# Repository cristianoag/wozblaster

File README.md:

# The Wozblaster (Reloaded)

## Introduction 
The WozBlaster OPL4 cartridge is a sound expansion device designed for the MSX platform. This cartridge enables a range of additional audio capabilities for the MSX, including support for both FM synthesis and wavetable synthesis. 

At its core is the OPL4 (FM Operator Type-L4) sound chip, which was developed by Yamaha and used in a variety of electronic musical instruments and computer sound cards. 

With the WozBlaster OPL4 cartridge, MSX computer users can enjoy high-quality sound and create complex musical arrangements with ease.

.jpg)

The WozBlaster cartridge is an external sound device designed for the MSX platform. It is a clone of the Moonsound and allows access to the advanced capabilities of the OPL4 sound chip for MSX games and other OPL4-compatible music software. The cartridge was originally designed by Gustavo Iriarte.

The OPL4 sound chip from Yamaha is typically paired with a YAC513 floating-point DAC chip, or an alternative compatible DAC chip. The YMF278 is an enhanced version of the OPL3 and, although not officially part of the standard, has been widely adopted by the MSX community, particularly in Europe.

Moonsound clones generally come equipped with 1 MB of sample-RAM and a 2 MB Yamaha YRW801-M General MIDI ROM. Although the board has the capacity to address more than 1 MB of memory, the original version of the Wozblaster only had two 512K memory chips.

It's worth noting that the original Wozblaster PCB cannot be fitted into a traditional MSX cartridge case. Additionally, as detailed in the building instructions, the audio jack holes on the original board are quite small, which made it difficult to find a connector that would fit.

## Original Wozblaster

Image below shows the original Wozblaster cartridge PCB:

|PCB Side 1|PCB Side 2|
|---|---|
|.jpg)|.jpg)|

A few reloaded versions of the WozBlaster cartridge have been created with appropriately-sized holes to fit both Konami and Patola cartridge cases. Additionally, the audio jack holes have been enlarged to accommodate most common audio jack connectors. Some versions of the cartridge are still a work in progress.

## Reloaded Versions

Currently, the following versions of the WozBlaster cartridge are available (please note that this list is subject to change as new versions become available):

* [Wozblaster Reloaded v1.1](/hardware/reloaded_v1.1) - Based on the original circuit, this version features a combination of through-hole and surface-mount components. The board is smaller and can fit in both Konami and Patola cases. (tested and working)

|PCB Side 1|PCB Side 2|
|---|---|
|.jpg)|.jpg)|

* [Wozblaster Reloaded v1.3](/hardware/reloaded_v1.3) - This version replaces the old 27C160 EPROM with an AM29F016B flash memory, and all passive components are 0603 SMD. The sound is injected back to SOUNDIN in mono. The board is smaller and can fit in both Konami and Patola cases. (abandoned)
  
* [Wozblaster Reloaded v3.3](/hardware/reloaded_v3.3/) - Version based on the UDA1334 DAC, and using the [Adafruit A1334 DAC Module](https://github.com/adafruit/Adafruit-UDA1334A-I2S-Stereo-DAC-PCB) to perform the digital to analog conversion. It is injecting audio back into the SOUNDIN MSX pin. It features 1MB of RAM and 2MB of ROM with MIDI compatible samples. (tested and working)

|PCB Side 1|PCB Side 2|
|---|---|
|||

* [Wozblaster Reloaded v4.0](/hardware/reloaded_v4.0/) - Evolution of v3.3 featuring a 2MB CY62167ELL RAM integrated. It also mixes the computer SOUNDIN. (tested and working)

|PCB Side 1|PCB Side 2|
|---|---|
|.jpg)|.jpg)|

* [Wozblaster Reloaded v4.5](/hardware/reloaded_v4.5/) - This version is now using the EPM7064STC44 (or EPM7032STC400) CPLD to replace the GAL16V8D it also better isolates the audio channels  before injecting them as mono back to the MSX SOUNDIN. (tested and working)

|PCB Side 1|PCB Side 2|
|---|---|
|.jpg)|.jpg)|

## Bill of Materials

The Bill of Materials (BOM) for each version of the WozBlaster cartridge is available in the respective page. The BOM includes a list of all the components needed to build the cartridge, as well as links to purchase the components online.

## Box and Inlay Trays

The Wozblaster Reloaded has a box designed by Adriano Souza to fit the cartridge. The box is available in the [box](/box) folder.

Although a paper inlay is provided to secure the cartridge inside the box, it is  recommended to use a plastic insert inner tray (bed) for additional protection, especially during transportation. These trays can be purchased from AliExpress at the following link: [AliExpress Tray](https://s.click.aliexpress.com/e/_DDVBv2D).

## Resources

This GitHub repository contains all of the resources needed to build both the original WozBlaster cartridge and the reloaded versions. For detailed instructions, you can refer to the article I wrote, which includes an updated bill of materials (BOM) with links to purchase the required components. You can find the article at https://theretrohacker.com/2022/12/31/blasting-sound-for-your-msx-the-wozblaster-reloaded/.

The update on the v3.1 development has been posted on a short YouTube video in english [here](https://youtu.be/J95RrFSF2NM). 

The update on v3.2 is available on a quick video [here](https://www.youtube.com/shorts/V5VmL33uvzE). 

Each folder contains detailed Bill of Materials for each version of the board, as well as the Gerber files needed to manufacture the PCBs. 

## License 

This work is licensed under a [Creative Commons Attribution-NonCommercial-ShareAlike 4.0 International License](http://creativecommons.org/licenses/by-nc-sa/4.0/).

* If you remix, transform, or build upon the material, you must distribute your contributions under the same license as the original.
* You may not use the material for commercial purposes.
* You must give appropriate credit, provide a link to the license, and indicate if changes were made. You may do so in any reasonable manner, but not in any way that suggests the licensor endorses you or your use.

**ATTENTION**

This project was made for the retro community and not for commercial purposes. So only retro hardware forums and individual people can build this project.

THE SALE OF ANY PART OF THIS PROJECT WITHOUT EXPRESS AUTHORIZATION IS PROHIBITED!

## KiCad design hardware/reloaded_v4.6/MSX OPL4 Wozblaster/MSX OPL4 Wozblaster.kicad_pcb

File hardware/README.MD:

# The Wozblaster (Reloaded)

## Content of this folder:

* [27C160 Adapter](/hardware/27c160-tl866-adapter) - This folder contains the files necessary to build an adapter that allows you to program the 27C160 EPROM on inexpensive TL866 programmers.
* [GAL16V8 JEDEC](/hardware/gal16v8d) - This folder contains the fuse file required to program the GAL16V8 SPLD with the selection circuit needed for the Wozblasters.
* [YRW801-M ROM] - This folder contains the binary content needed to program flash or EPROMs with the contents of the YRW801-M (MIDI Samples).
* [Wozblaster v1](hardware/v1) - This folder contains the original Wozblaster board created by Gustavo Iriarte. (Released)
* [Wozblaster Reloaded v1.1](/hardware/reloaded_v1.1) - Based on the original circuit, this version features a combination of through-hole and surface-mount components. The board is smaller and can fit in both Konami and Patola cases. (Released)
* [Wozblaster Reloaded v1.2](/hardware/reloaded_v1.2) - This version replaces the old 27C160 EPROM with an AM29F016B flash, and all passive components are 0603 SMD. The sound is injected back to SOUNDIN in mono. The board is smaller and can fit in both Konami and Patola cases. (In development)
* [Wozblaster Reloaded v2.0](/hardware/reloaded_v2) - This version features an AM29F016B flash in place of the 27C160 EPROM, all passive components are 0603 SMD, and the YAC513 DAC is replaced by a NEC UPD6376. The sound is injected back to SOUNDIN in mono, and the LF347 OP Amps are replaced with 4558s. The audio circuit has been improved, and the board is smaller and can fit in both Konami and Patola cases. (In development)

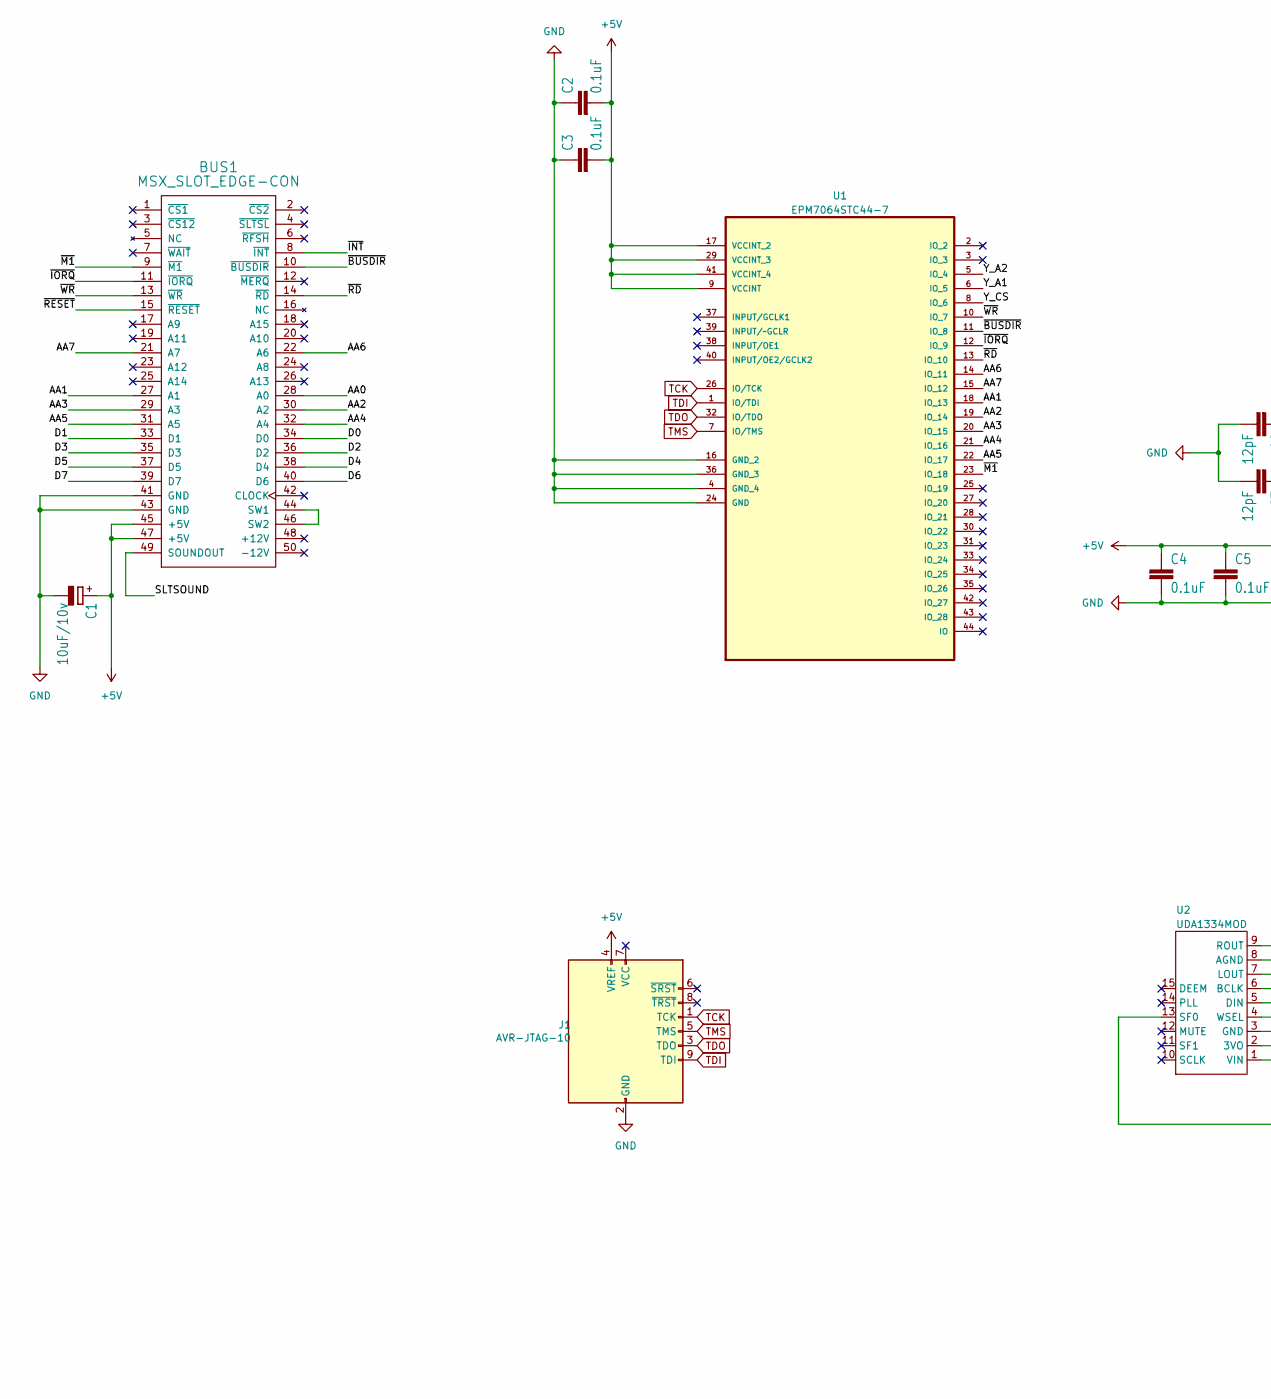
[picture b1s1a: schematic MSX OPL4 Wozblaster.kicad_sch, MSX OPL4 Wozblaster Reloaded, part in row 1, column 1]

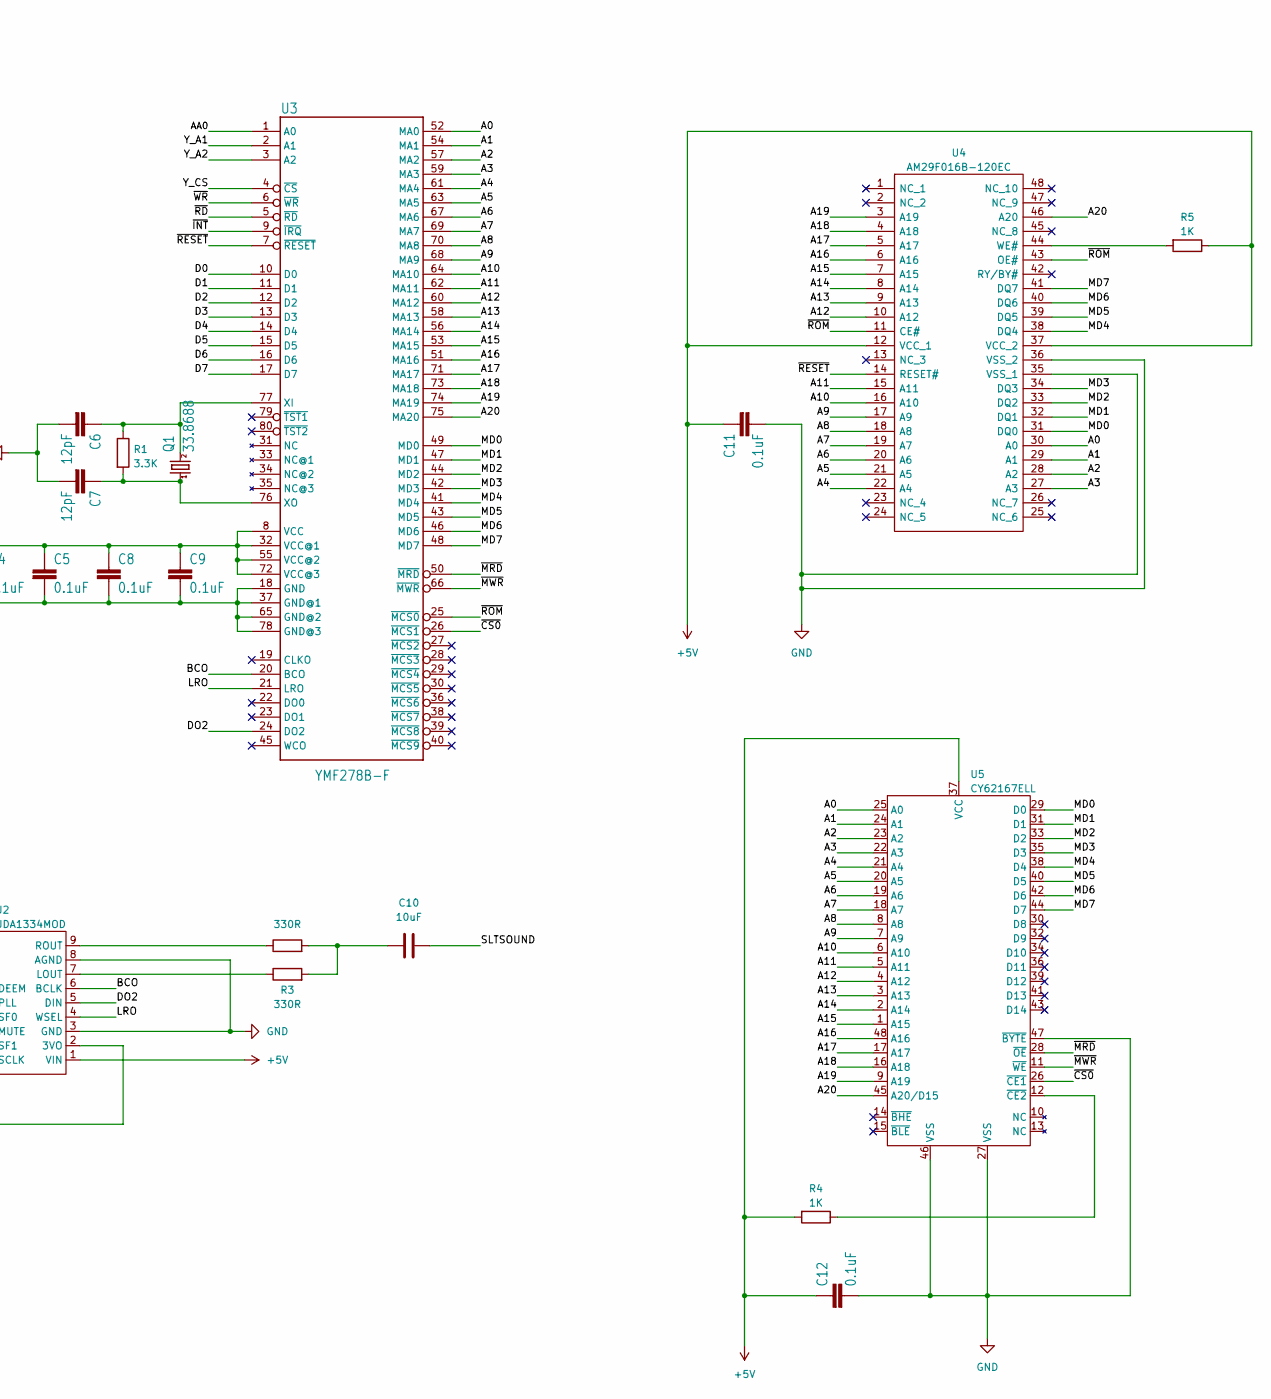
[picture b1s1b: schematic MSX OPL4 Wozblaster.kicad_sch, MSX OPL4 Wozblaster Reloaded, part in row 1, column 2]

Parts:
BUS1: MSX_SLOT_EDGE-CON; msx_cartridge; MPN n/a
C1: 10uF/10v; CP_EIA-3216-18_Kemet-A
C2, C3, C4, C5, C8, C9, C11, C12: 0.1uF; C_0603_1608Metric
C6, C7: 12pF; C_0603_1608Metric
C10: 10uF; C_0603_1608Metric
J1: AVR-JTAG-10; PinHeader_2x05_P2.54mm_Vertical
Q1: 33.8688; Crystal_HC49-U_Vertical
R1: 3.3K; R_0603_1608Metric
R2, R3: 330R; R_0603_1608Metric
R4, R5: 1K; R_0603_1608Metric
U1: EPM7064STC44-7; QFP80P1200X1200X120-44N; MPN EPM7064STC44-7
U2: UDA1334MOD
U3: YMF278B-F; 80-QFP
U4: AM29F016B-120EC; SOP50P2000X120-48N; Manufacturer_Part_Number AM29F016B-120EC
U5: CY62167ELL; SOP50P2000X120-48N

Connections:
+5V: BUS1.45 (+5V), BUS1.47 (+5V), C1.1 (+), C2.2, C3.2, C4.1, C5.1, C8.1, C9.1, C11.1, C12.1, J1.4 (VREF), R4.2, R5.1, U1.9 (VCCINT), U1.17 (VCCINT_2), U1.29 (VCCINT_3), U1.41 (VCCINT_4), U2.1 (VIN), U3.8 (VCC), U3.32 (VCC@1), U3.55 (VCC@2), U3.72 (VCC@3), U4.12 (VCC_1), U4.37 (VCC_2), U5.37 (VCC)
/A0: U3.52 (MA0), U4.30 (A0), U5.25 (A0)
/A1: U3.54 (MA1), U4.29 (A1), U5.24 (A1)
/A2: U3.57 (MA2), U4.28 (A2), U5.23 (A2)
/A3: U3.59 (MA3), U4.27 (A3), U5.22 (A3)
/A4: U3.61 (MA4), U4.22 (A4), U5.21 (A4)
/A5: U3.63 (MA5), U4.21 (A5), U5.20 (A5)
/A6: U3.67 (MA6), U4.20 (A6), U5.19 (A6)
/A7: U3.69 (MA7), U4.19 (A7), U5.18 (A7)
/A8: U3.70 (MA8), U4.18 (A8), U5.8 (A8)
/A9: U3.68 (MA9), U4.17 (A9), U5.7 (A9)
/A10: U3.64 (MA10), U4.16 (A10), U5.6 (A10)
/A11: U3.62 (MA11), U4.15 (A11), U5.5 (A11)
/A12: U3.60 (MA12), U4.10 (A12), U5.4 (A12)
/A13: U3.58 (MA13), U4.9 (A13), U5.3 (A13)
/A14: U3.56 (MA14), U4.8 (A14), U5.2 (A14)
/A15: U3.53 (MA15), U4.7 (A15), U5.1 (A15)
/A16: U3.51 (MA16), U4.6 (A16), U5.48 (A16)
/A17: U3.71 (MA17), U4.5 (A17), U5.17 (A17)
/A18: U3.73 (MA18), U4.4 (A18), U5.16 (A18)
/A19: U3.74 (MA19), U4.3 (A19), U5.9 (A19)
/A20: U3.75 (MA20), U4.46 (A20), U5.45 (A20/D15)
/AA0: BUS1.28 (A0), U3.1 (A0)
/AA1: BUS1.27 (A1), U1.18 (IO_13)
/AA2: BUS1.30 (A2), U1.19 (IO_14)
/AA3: BUS1.29 (A3), U1.20 (IO_15)
/AA4: BUS1.32 (A4), U1.21 (IO_16)
/AA5: BUS1.31 (A5), U1.22 (IO_17)
/AA6: BUS1.22 (A6), U1.14 (IO_11)
/AA7: BUS1.21 (A7), U1.15 (IO_12)
/BCO: U2.6 (BCLK), U3.20 (BCO)
/D0: BUS1.34 (D0), U3.10 (D0)
/D1: BUS1.33 (D1), U3.11 (D1)
/D2: BUS1.36 (D2~), U3.12 (D2)
/D3: BUS1.35 (D3), U3.13 (D3)
/D4: BUS1.38 (D4), U3.14 (D4)
/D5: BUS1.37 (D5), U3.15 (D5)
/D6: BUS1.40 (D6), U3.16 (D6)
/D7: BUS1.39 (D7), U3.17 (D7)
/DO2: U2.5 (DIN), U3.24 (DO2)
/LRO: U2.4 (WSEL), U3.21 (LRO)
/MD0: U3.49 (MD0), U4.31 (DQ0), U5.29 (D0)
/MD1: U3.47 (MD1), U4.32 (DQ1), U5.31 (D1)
/MD2: U3.44 (MD2), U4.33 (DQ2), U5.33 (D2)
/MD3: U3.42 (MD3), U4.34 (DQ3), U5.35 (D3)
/MD4: U3.41 (MD4), U4.38 (DQ4), U5.38 (D4)
/MD5: U3.43 (MD5), U4.39 (DQ5), U5.40 (D5)
/MD6: U3.46 (MD6), U4.40 (DQ6), U5.42 (D6)
/MD7: U3.48 (MD7), U4.41 (DQ7), U5.44 (D7)
/SLTSOUND: BUS1.49 (SOUNDOUT), C10.2
/Y_A1: U1.6 (IO_5), U3.2 (A1)
/Y_A2: U1.5 (IO_4), U3.3 (A2)
/Y_CS: U1.8 (IO_6), U3.4 (~CS)
/~BUSDIR: BUS1.10 (~BUSDIR), U1.11 (IO_8)
/~CS0: U3.26 (~MCS1), U5.26 (~CE1)
/~INT: BUS1.8 (~INT), U3.9 (~IRQ)
/~IORQ: BUS1.11 (~IORQ), U1.12 (IO_9)
/~M1: BUS1.9 (~M1), U1.23 (IO_18)
/~MRD: U3.50 (~MRD), U5.28 (~OE)
/~MWR: U3.66 (~MWR), U5.11 (~WE)
/~RD: BUS1.14 (~RD), U1.13 (IO_10), U3.5 (~RD)
/~RESET: BUS1.15 (~RESET), U3.7 (~RESET), U4.14 (RESET#)
/~ROM: U3.25 (~MCS0), U4.11 (CE#), U4.43 (OE#)
/~WR: BUS1.13 (~WR), U1.10 (IO_7), U3.6 (~WR)
GND: BUS1.41 (GND), BUS1.43 (GND), C1.2 (-), C2.1, C3.1, C4.2, C5.2, C6.2, C7.2, C8.2, C9.2, C11.2, C12.2, J1.2 (GND), J1.10 (GND), U1.4 (GND_4), U1.16 (GND_2), U1.24 (GND), U1.36 (GND_3), U2.3 (GND), U2.8 (AGND), U3.18 (GND), U3.37 (GND@1), U3.65 (GND@2), U3.78 (GND@3), U4.35 (VSS_1), U4.36 (VSS_2), U5.27 (VSS), U5.46 (VSS), U5.47 (~BYTE)
unnamed: BUS1.44 (SW1), BUS1.46 (SW2)
unnamed: C10.1, R2.2, R3.2
unnamed: U2.2 (3VO), U2.13 (SF0)
unnamed: R3.1, U2.7 (LOUT)
unnamed: R2.1, U2.9 (ROUT)
unnamed: C6.1, Q1.2, R1.1, U3.77 (XI)
unnamed: C7.1, Q1.1, R1.2, U3.76 (XO)
unnamed: R5.2, U4.44 (WE#)
unnamed: R4.1, U5.12 (~CE2)
TCK: J1.1 (TCK), U1.26 (IO/TCK)
TDI: J1.9 (TDI), U1.1 (IO/TDI)
TDO: J1.3 (TDO), U1.32 (IO/TDO)
TMS: J1.5 (TMS), U1.7 (IO/TMS)

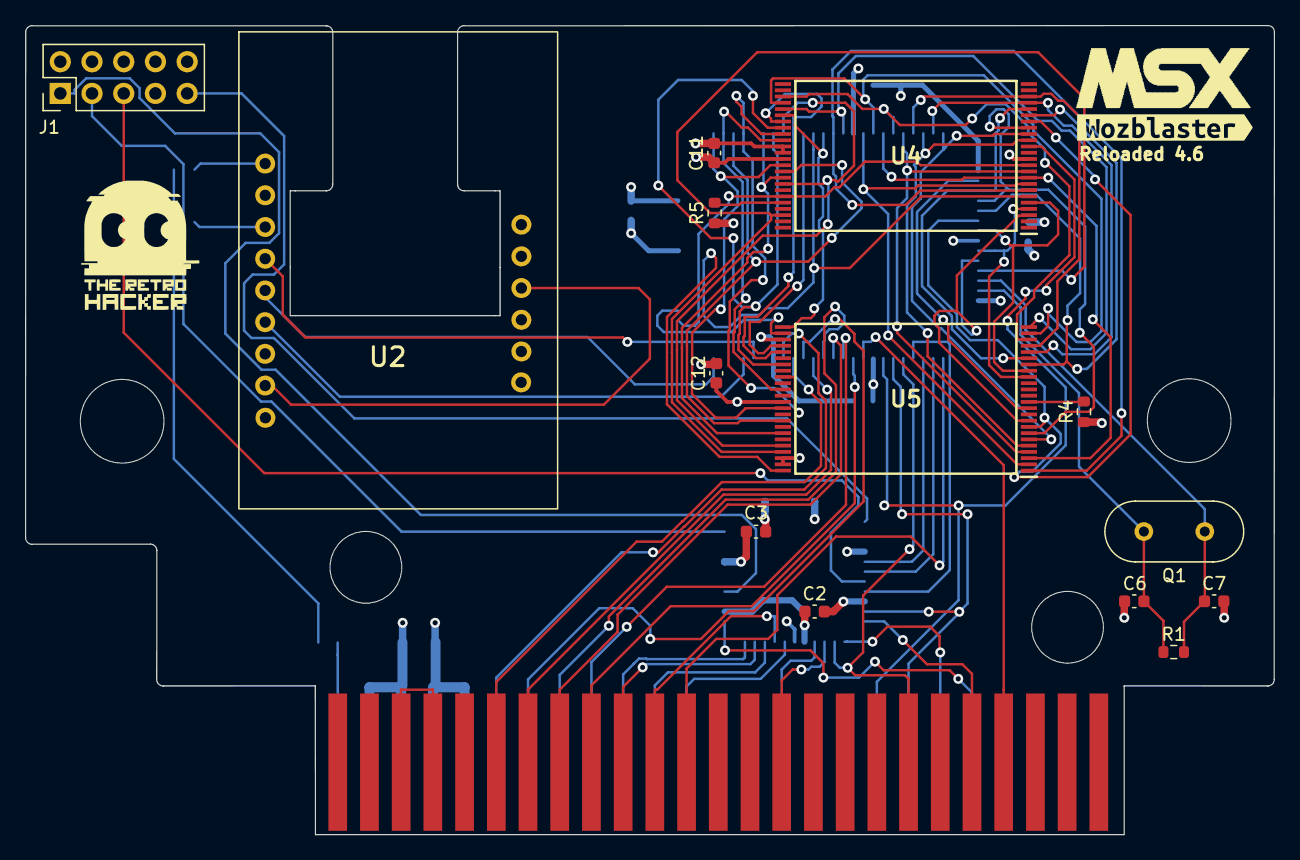
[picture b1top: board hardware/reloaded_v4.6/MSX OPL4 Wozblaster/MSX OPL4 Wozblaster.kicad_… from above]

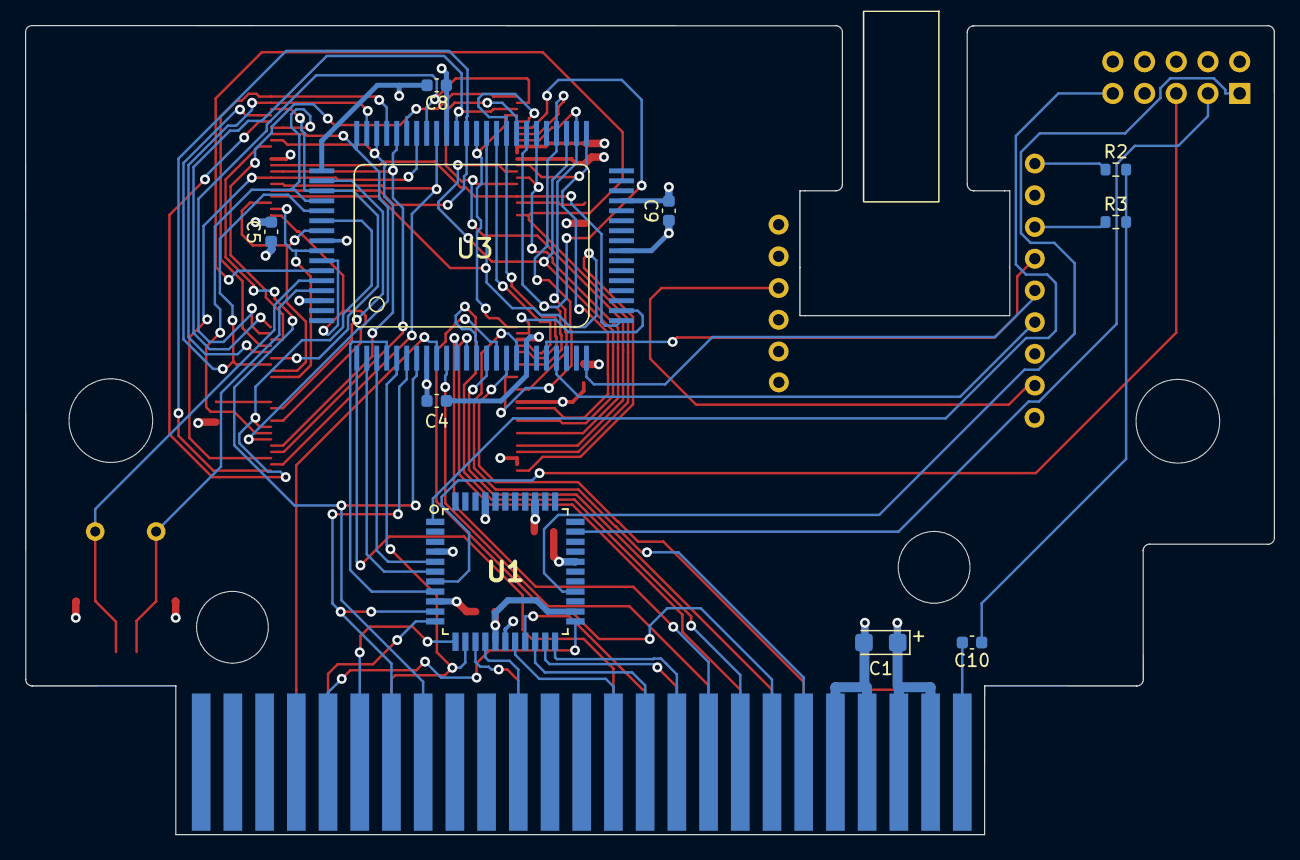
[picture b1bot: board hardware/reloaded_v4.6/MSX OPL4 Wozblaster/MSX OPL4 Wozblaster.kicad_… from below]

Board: 4 copper layers, 100.0 x 64.8 mm, 27 parts (11 on the bottom side), 78 nets.

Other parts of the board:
LOGO_MSX: LOGO_MSX
kibuzzard-670C230B: G***; kibuzzard-670C230B

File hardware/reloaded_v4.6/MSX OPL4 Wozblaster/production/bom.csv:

Designator,Footprint,Quantity,Value,LCSC Part #
C1,CP_EIA-3216-18_Kemet-A,1,10uF/10v,
C10,0603,1,10uF,
"C11, C12, C2, C3, C4, C5, C8, C9",0603,8,0.1uF,
"C6, C7",0603,2,12pF,
J1,PinHeader_2x05_P2.54mm_Vertical,1,AVR-JTAG-10,
LOGO_MSX,LOGO_MSX,1,,
Q1,Crystal_HC49-U_Vertical,1,33.8688,
R1,0603,1,3.3K,
"R2, R3",0603,2,330R,
"R4, R5",0603,2,1K,
U1,QFP80P1200X1200X120-44N,1,EPM7064STC44-7,EPM7064STC44-7
U2,UDA1334MOD,1,UDA1334MOD,
U3,80-QFP,1,YMF278B-F,
U4,SOP50P2000X120-48N,1,AM29F016B-120EC,
U5,SOP50P2000X120-48N,1,CY62167ELL,

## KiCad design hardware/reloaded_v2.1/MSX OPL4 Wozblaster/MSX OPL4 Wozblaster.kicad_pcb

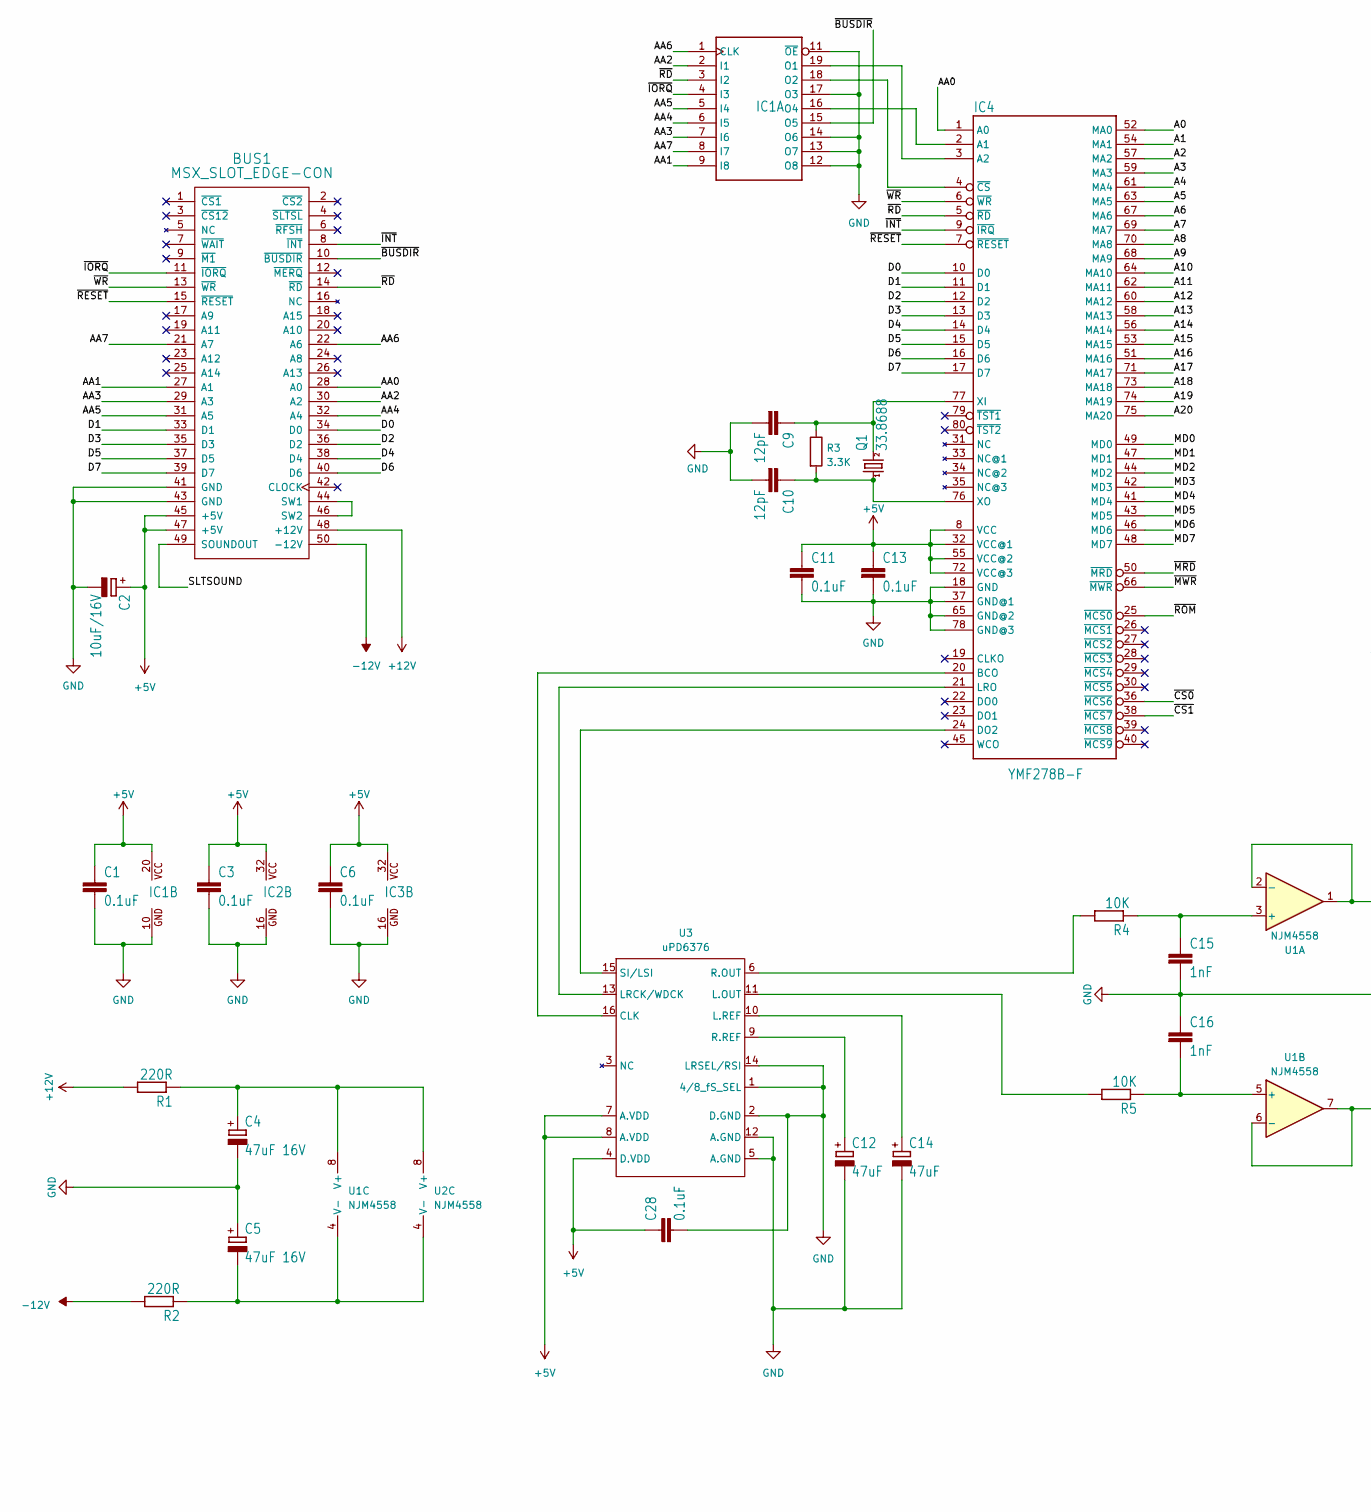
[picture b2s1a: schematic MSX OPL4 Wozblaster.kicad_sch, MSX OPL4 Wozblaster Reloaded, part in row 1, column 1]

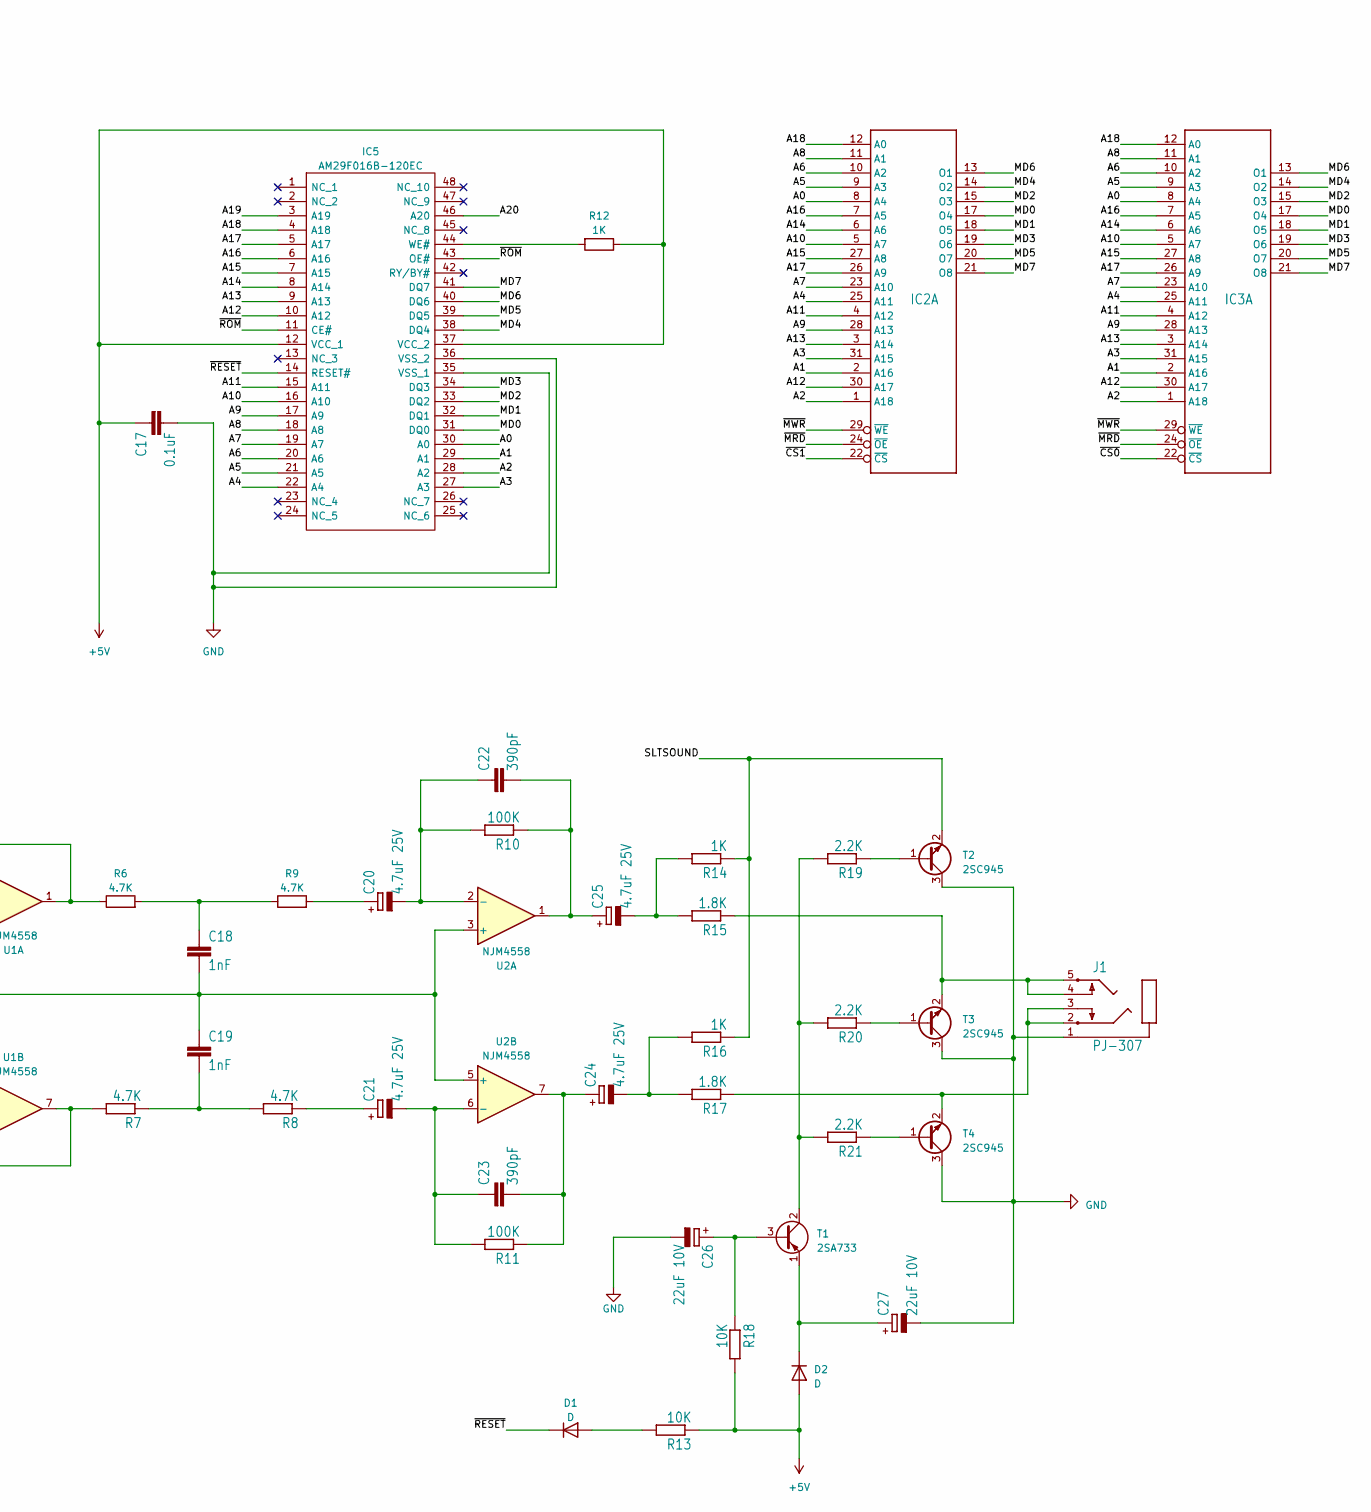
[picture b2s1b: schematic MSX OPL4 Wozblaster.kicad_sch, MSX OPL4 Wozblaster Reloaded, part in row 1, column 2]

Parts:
BUS1: MSX_SLOT_EDGE-CON; msx_cartridge; MPN n/a
C1, C3, C6, C11, C13, C17, C28: 0.1uF; C_0603_1608Metric
C2: 10uF/16V; CP_EIA-3528-21_Kemet-B
C4, C5: 47uF 16V; CP_EIA-3528-21_Kemet-B
C9, C10: 12pF; C_0603_1608Metric
C12, C14: 47uF; CP_EIA-3528-21_Kemet-B
C15, C16, C18, C19: 1nF; C_0603_1608Metric
C20, C21, C24, C25: 4.7uF 25V; CP_EIA-3216-18_Kemet-A
C22, C23: 390pF; C_0603_1608Metric
C26, C27: 22uF 10V; CP_EIA-3528-21_Kemet-B
D1, D2: D; D_A-405_P7.62mm_Horizontal
IC1: GAL16V8D; DIL20
IC2, IC3: KM684000ALG; SOP32L
IC4: YMF278B-F; 80-QFP
IC5: AM29F016B-120EC; SOP50P2000X120-48N; Manufacturer_Part_Number AM29F016B-120EC
J1: PJ-307
Q1: 33.8688; Crystal_HC49-U_Vertical
R1, R2: 220R; R_0603_1608Metric
R3: 3.3K; R_0603_1608Metric
R4, R5, R13, R18: 10K; R_0603_1608Metric
R6, R7, R8, R9: 4.7K; R_0603_1608Metric
R10, R11: 100K; R_0603_1608Metric
R12, R14, R16: 1K; R_0603_1608Metric
R15, R17: 1.8K; R_0603_1608Metric
R19, R20, R21: 2.2K; R_0603_1608Metric
T1: 2SA733; SOT-23
T2, T3, T4: 2SC945; SOT-23
U1, U2: NJM4558; SO-8_5.3x6.2mm_P1.27mm
U3: uPD6376; SO-16_5.3x10.2mm_P1.27mm

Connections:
+5V: BUS1.45 (+5V), BUS1.47 (+5V), C1.1, C2.1 (+), C3.1, C6.1, C11.1, C13.1, C17.1, C28.1, D2.2 (A), IC1.20 (VCC), IC2.32 (VCC), IC3.32 (VCC), IC4.8 (VCC), IC4.32 (VCC@1), IC4.55 (VCC@2), IC4.72 (VCC@3), IC5.12 (VCC_1), IC5.37 (VCC_2), R12.1, R13.1, R18.2, U3.4 (D.VDD), U3.7 (A.VDD), U3.8 (A.VDD)
+12V: BUS1.48 (+12V), R1.2
-12V: BUS1.50 (-12V), R2.2
/A0: IC2.8 (A4), IC3.8 (A4), IC4.52 (MA0), IC5.30 (A0)
/A1: IC2.2 (A16), IC3.2 (A16), IC4.54 (MA1), IC5.29 (A1)
/A2: IC2.1 (A18), IC3.1 (A18), IC4.57 (MA2), IC5.28 (A2)
/A3: IC2.31 (A15), IC3.31 (A15), IC4.59 (MA3), IC5.27 (A3)
/A4: IC2.25 (A11), IC3.25 (A11), IC4.61 (MA4), IC5.22 (A4)
/A5: IC2.9 (A3), IC3.9 (A3), IC4.63 (MA5), IC5.21 (A5)
/A6: IC2.10 (A2), IC3.10 (A2), IC4.67 (MA6), IC5.20 (A6)
/A7: IC2.23 (A10), IC3.23 (A10), IC4.69 (MA7), IC5.19 (A7)
/A8: IC2.11 (A1), IC3.11 (A1), IC4.70 (MA8), IC5.18 (A8)
/A9: IC2.28 (A13), IC3.28 (A13), IC4.68 (MA9), IC5.17 (A9)
/A10: IC2.5 (A7), IC3.5 (A7), IC4.64 (MA10), IC5.16 (A10)
/A11: IC2.4 (A12), IC3.4 (A12), IC4.62 (MA11), IC5.15 (A11)
/A12: IC2.30 (A17), IC3.30 (A17), IC4.60 (MA12), IC5.10 (A12)
/A13: IC2.3 (A14), IC3.3 (A14), IC4.58 (MA13), IC5.9 (A13)
/A14: IC2.6 (A6), IC3.6 (A6), IC4.56 (MA14), IC5.8 (A14)
/A15: IC2.27 (A8), IC3.27 (A8), IC4.53 (MA15), IC5.7 (A15)
/A16: IC2.7 (A5), IC3.7 (A5), IC4.51 (MA16), IC5.6 (A16)
/A17: IC2.26 (A9), IC3.26 (A9), IC4.71 (MA17), IC5.5 (A17)
/A18: IC2.12 (A0), IC3.12 (A0), IC4.73 (MA18), IC5.4 (A18)
/A19: IC4.74 (MA19), IC5.3 (A19)
/A20: IC4.75 (MA20), IC5.46 (A20)
/AA0: BUS1.28 (A0), IC4.1 (A0)
/AA1: BUS1.27 (A1), IC1.9 (I8)
/AA2: BUS1.30 (A2), IC1.2 (I1)
/AA3: BUS1.29 (A3), IC1.7 (I6)
/AA4: BUS1.32 (A4), IC1.6 (I5)
/AA5: BUS1.31 (A5), IC1.5 (I4)
/AA6: BUS1.22 (A6), IC1.1 (CLK)
/AA7: BUS1.21 (A7), IC1.8 (I7)
/D0: BUS1.34 (D0), IC4.10 (D0)
/D1: BUS1.33 (D1), IC4.11 (D1)
/D2: BUS1.36 (D2~), IC4.12 (D2)
/D3: BUS1.35 (D3), IC4.13 (D3)
/D4: BUS1.38 (D4), IC4.14 (D4)
/D5: BUS1.37 (D5), IC4.15 (D5)
/D6: BUS1.40 (D6), IC4.16 (D6)
/D7: BUS1.39 (D7), IC4.17 (D7)
/MD0: IC2.17 (O4), IC3.17 (O4), IC4.49 (MD0), IC5.31 (DQ0)
/MD1: IC2.18 (O5), IC3.18 (O5), IC4.47 (MD1), IC5.32 (DQ1)
/MD2: IC2.15 (O3), IC3.15 (O3), IC4.44 (MD2), IC5.33 (DQ2)
/MD3: IC2.19 (O6), IC3.19 (O6), IC4.42 (MD3), IC5.34 (DQ3)
/MD4: IC2.14 (O2), IC3.14 (O2), IC4.41 (MD4), IC5.38 (DQ4)
/MD5: IC2.20 (O7), IC3.20 (O7), IC4.43 (MD5), IC5.39 (DQ5)
/MD6: IC2.13 (O1), IC3.13 (O1), IC4.46 (MD6), IC5.40 (DQ6)
/MD7: IC2.21 (O8), IC3.21 (O8), IC4.48 (MD7), IC5.41 (DQ7)
/SLTSOUND: BUS1.49 (SOUNDOUT), R14.1, R16.1, T2.2 (E)
/~BUSDIR: BUS1.10 (~BUSDIR), IC1.15 (O5)
/~CS0: IC3.22 (~CS), IC4.36 (~MCS6)
/~CS1: IC2.22 (~CS), IC4.38 (~MCS7)
/~INT: BUS1.8 (~INT), IC4.9 (~IRQ)
/~IORQ: BUS1.11 (~IORQ), IC1.4 (I3)
/~MRD: IC2.24 (~OE), IC3.24 (~OE), IC4.50 (~MRD)
/~MWR: IC2.29 (~WE), IC3.29 (~WE), IC4.66 (~MWR)
/~RD: BUS1.14 (~RD), IC1.3 (I2), IC4.5 (~RD)
/~RESET: BUS1.15 (~RESET), D1.1 (K), IC4.7 (~RESET), IC5.14 (RESET#)
/~ROM: IC4.25 (~MCS0), IC5.11 (CE#), IC5.43 (OE#)
/~WR: BUS1.13 (~WR), IC4.6 (~WR)
GND: BUS1.41 (GND), BUS1.43 (GND), C1.2, C2.2 (-), C3.2, C4.2 (-), C5.1 (+), C6.2, C9.2, C10.2, C11.2, C12.2 (-), C13.2, C14.2 (-), C15.2, C16.1, C17.2, C18.2, C19.1, C26.2 (-), C27.2 (-), C28.2, IC1.10 (GND), IC1.11 (~OE), IC1.12 (O8), IC1.13 (O7), IC1.14 (O6), IC1.17 (O3), IC2.16 (GND), IC3.16 (GND), IC4.18 (GND), IC4.37 (GND@1), IC4.65 (GND@2), IC4.78 (GND@3), IC5.35 (VSS_1), IC5.36 (VSS_2), J1.1, T2.3 (C), T3.3 (C), T4.3 (C), U2.3 (+), U2.5 (+), U3.1 (4/8_fS_SEL), U3.2 (D.GND), U3.5 (A.GND), U3.12 (A.GND), U3.14 (LRSEL/RSI)
unnamed: BUS1.44 (SW1), BUS1.46 (SW2)
unnamed: C4.1 (+), R1.1, U1.8 (V+), U2.8 (V+)
unnamed: C5.2 (-), R2.1, U1.4 (V-), U2.4 (V-)
unnamed: C12.1 (+), U3.9 (R.REF)
unnamed: C14.1 (+), U3.10 (L.REF)
unnamed: C18.1, R6.2, R9.1
unnamed: C19.2, R7.1, R8.2
unnamed: C20.1 (+), R9.2
unnamed: C20.2 (-), C22.1, R10.2, U2.2 (-)
unnamed: C21.1 (+), R8.1
unnamed: C21.2 (-), C23.1, R11.2, U2.6 (-)
unnamed: C23.2, C24.1 (+), R11.1, U2.7
unnamed: C24.2 (-), R16.2, R17.2
unnamed: C22.2, C25.1 (+), R10.1, U2.1
unnamed: C25.2 (-), R14.2, R15.2
unnamed: C26.1 (+), R18.1, T1.3 (B)
unnamed: C27.1 (+), D2.1 (K), T1.1 (E)
unnamed: D1.2 (A), R13.2
unnamed: IC1.19 (O1), IC4.3 (A2)
unnamed: IC1.18 (O2), IC4.4 (~CS)
unnamed: IC1.16 (O4), IC4.2 (A1)
unnamed: IC4.20 (BCO), U3.16 (CLK)
unnamed: IC4.24 (DO2), U3.15 (SI/LSI)
unnamed: IC4.21 (LRO), U3.13 (LRCK/WDCK)
unnamed: C9.1, IC4.77 (XI), Q1.2, R3.1
unnamed: C10.1, IC4.76 (XO), Q1.1, R3.2
unnamed: IC5.44 (WE#), R12.2
unnamed: R19.2, R20.2, R21.2, T1.2 (C)
unnamed: R19.1, T2.1 (B)
unnamed: R20.1, T3.1 (B)
unnamed: J1.4, J1.5, R15.1, T3.2 (E)
unnamed: R21.1, T4.1 (B)
unnamed: J1.2, J1.3, R17.1, T4.2 (E)
unnamed: C15.1, R4.1, U1.3 (+)
unnamed: R6.1, U1.1, U1.2 (-)
unnamed: C16.2, R5.1, U1.5 (+)
unnamed: R7.2, U1.6 (-), U1.7
unnamed: R5.2, U3.11 (L.OUT)
unnamed: R4.2, U3.6 (R.OUT)

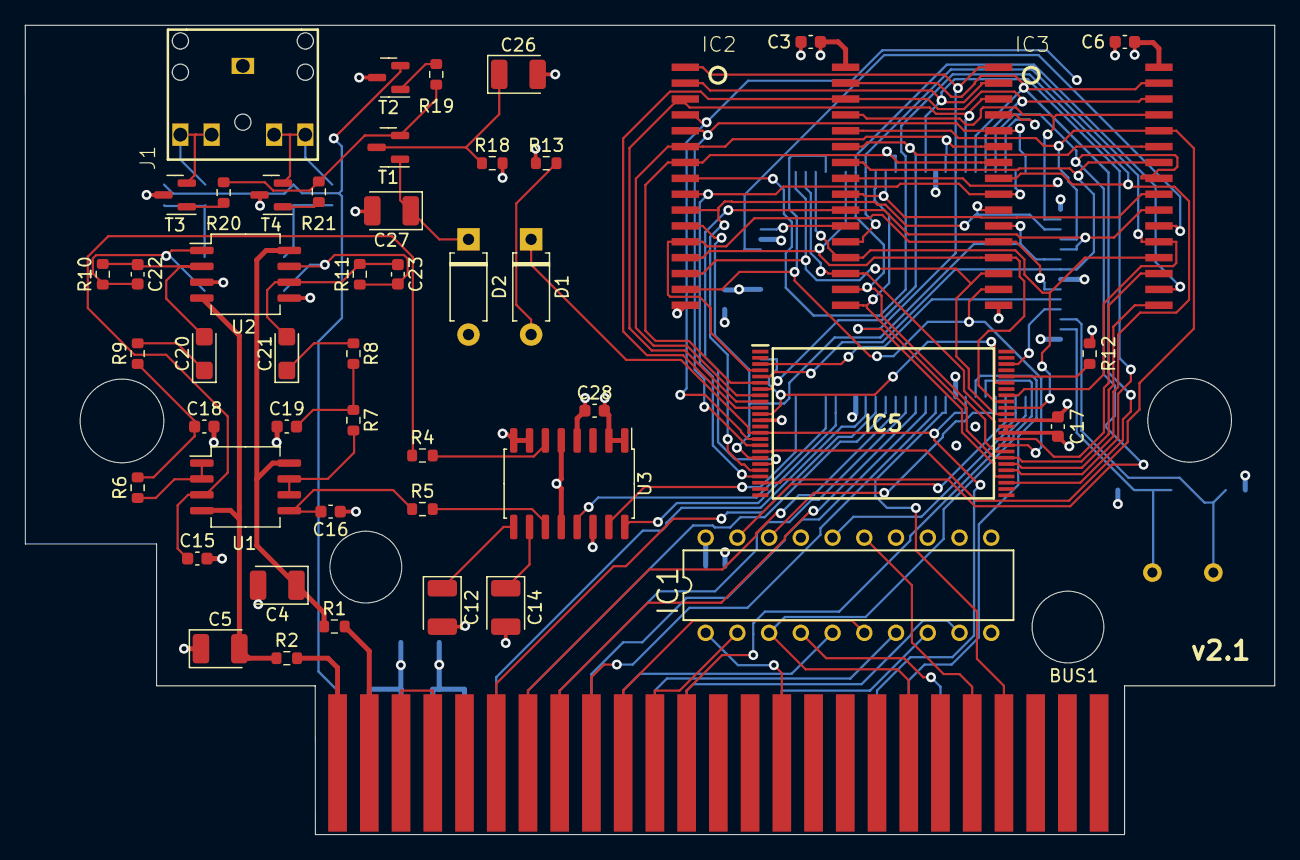
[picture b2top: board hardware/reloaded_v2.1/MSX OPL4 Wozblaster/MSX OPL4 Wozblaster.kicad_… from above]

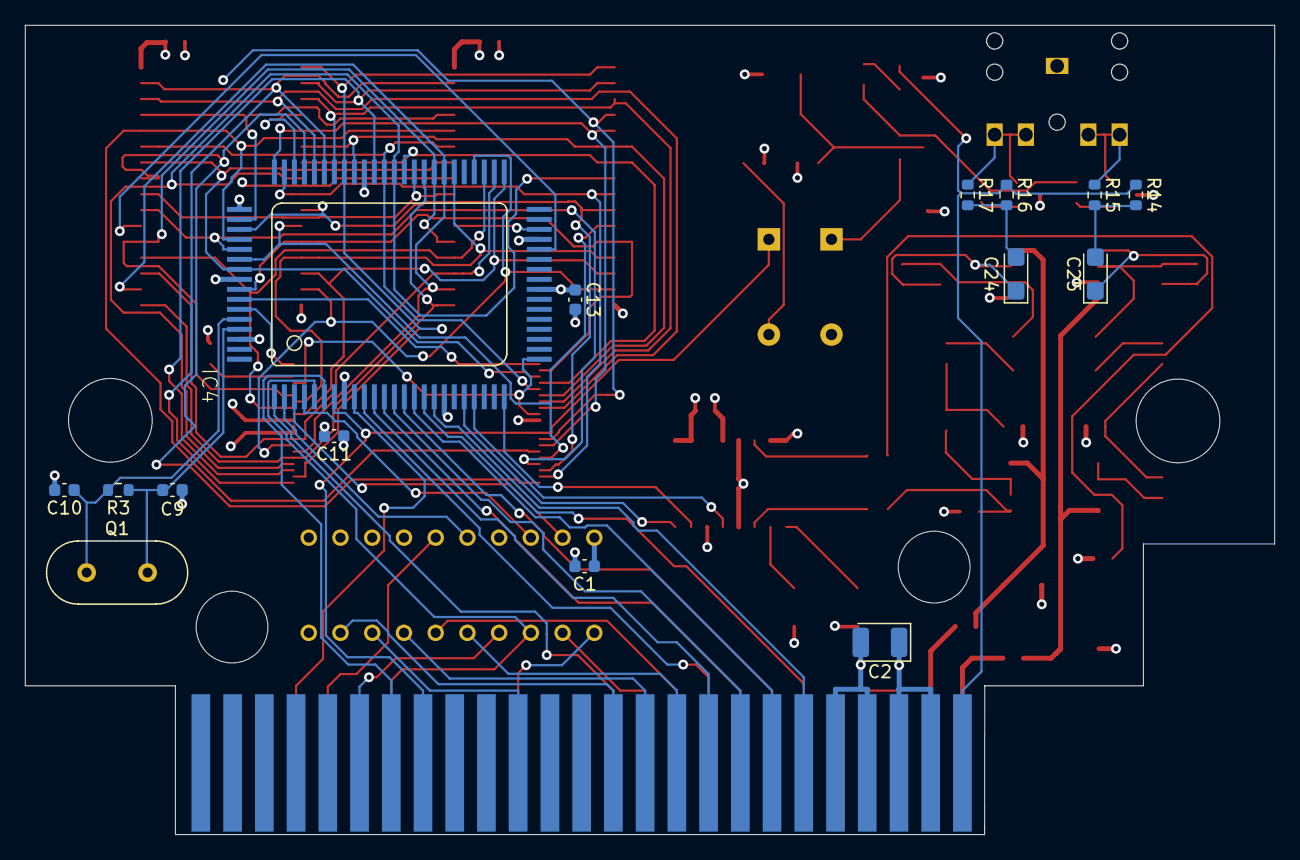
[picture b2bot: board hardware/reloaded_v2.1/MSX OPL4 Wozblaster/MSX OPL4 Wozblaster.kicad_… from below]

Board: 4 copper layers, 100.0 x 64.8 mm, 64 parts (15 on the bottom side), 100 nets.

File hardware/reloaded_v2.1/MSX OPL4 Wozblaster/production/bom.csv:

Designator,Footprint,Quantity,Value,LCSC Part #
C1,0603,1,0.1uF,
C10,0603,1,12pF,
C11,0603,1,0.1uF,
"C12, C14",CP_EIA-3528-21_Kemet-B,2,47uF,
C13,0603,1,0.1uF,
C15,0603,1,1nF,
C16,0603,1,1nF,
C17,0603,1,0.1uF,
C18,0603,1,1nF,
C19,0603,1,1nF,
C2,CP_EIA-3528-21_Kemet-B,1,10uF/16V,
"C20, C21, C24, C25",CP_EIA-3216-18_Kemet-A,4,4.7uF 25V,
C22,0603,1,390pF,
C23,0603,1,390pF,
"C26, C27",CP_EIA-3528-21_Kemet-B,2,22uF 10V,
C28,0603,1,0.1uF,
C3,0603,1,0.1uF,
"C4, C5",CP_EIA-3528-21_Kemet-B,2,47uF 16V,
C6,0603,1,0.1uF,
C9,0603,1,12pF,
"D1, D2",D_A-405_P7.62mm_Horizontal,2,D,
IC1,DIL20,1,GAL16V8D,
"IC2, IC3",SOP32L,2,KM684000ALG,
IC4,80-QFP,1,YMF278B-F,
IC5,SOP50P2000X120-48N,1,AM29F016B-120EC,
J1,PJ-307,1,PJ-307,
Q1,Crystal_HC49-U_Vertical,1,33.8688,
R1,0603,1,220R,
R10,0603,1,100K,
R11,0603,1,100K,
R12,0603,1,1K,
R13,0603,1,10K,
R14,0603,1,1K,
R15,0603,1,1.8K,
R16,0603,1,1K,
R17,0603,1,1.8K,
R18,0603,1,10K,
R19,0603,1,2.2K,
R2,0603,1,220R,
R20,0603,1,2.2K,
R21,0603,1,2.2K,
R3,0603,1,3.3K,
R4,0603,1,10K,
R5,0603,1,10K,
R6,0603,1,4.7K,
R7,0603,1,4.7K,
R8,0603,1,4.7K,
R9,0603,1,4.7K,
T1,SOT-23,1,2SA733,
"T2, T3, T4",SOT-23,3,2SC945,
"U1, U2",SO-8_5.3x6.2mm_P1.27mm,2,NJM4558,
U3,SO-16_5.3x10.2mm_P1.27mm,1,uPD6376,
